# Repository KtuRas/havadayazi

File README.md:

<h1>Arduino ile Havada Yazı</h1>

<p>Bu proje Arduino Günü için oluşturulmuştur.</p>
<p>Kendi etrafında dönebilen bir mekanızmaya bağlı 8 ledin, dönüş sırasında belirli bir düzene göre yüksek
    hızda yanıp sönmesi ile havada yazı oluşturma prensibine göre çalışır.
</p>
<p>Mekanizma dururken ledler yanıp sönsede yazıyı göz ile ayırt edebilmek mümkün değildir. Ancak mekanızma döndürülünce 
    ledler havada farklı yerlerde yanıp söneceğinden göz ile algılayabilmek mümkün olmaktadır.    
</p>

## Çalışma Prensibi
<p>Bir harf aşağıdaki şekilde Arduino' nun çıkışına aktarılmıştır. </p>

<table style="width: 197px; height: 207px;">
<tbody>
<tr>
<td style="width: 32px;">A&nbsp;</td>
<td style="width: 32px;">B&nbsp;</td>
<td style="width: 33px;">&nbsp;C</td>
<td style="width: 33px;">&nbsp;D</td>
<td style="width: 33px;">&nbsp;E</td>
<td style="width: 33px;">&nbsp;F</td>
</tr>
<tr>
<td style="width: 32px;">&nbsp;0</td>
<td style="width: 32px;">&nbsp;1</td>
<td style="width: 33px;">&nbsp;1&nbsp;</td>
<td style="width: 33px;">&nbsp;1&nbsp;</td>
<td style="width: 33px;">&nbsp;1&nbsp;</td>
<td style="width: 33px;">&nbsp;0&nbsp;</td>
</tr>
<tr>
<td style="width: 32px;">&nbsp;1&nbsp;</td>
<td style="width: 32px;">&nbsp;0</td>
<td style="width: 33px;">&nbsp;0&nbsp;</td>
<td style="width: 33px;">&nbsp;0</td>
<td style="width: 33px;">&nbsp;0&nbsp;</td>
<td style="width: 33px;">&nbsp;1&nbsp;</td>
</tr>
<tr>
<td style="width: 32px;">&nbsp;1&nbsp;</td>
<td style="width: 32px;">&nbsp;0&nbsp;</td>
<td style="width: 33px;">&nbsp;0&nbsp;</td>
<td style="width: 33px;">&nbsp;0&nbsp;</td>
<td style="width: 33px;">&nbsp;0&nbsp;</td>
<td style="width: 33px;">&nbsp;1&nbsp;</td>
</tr>
<tr>
<td style="width: 32px;">&nbsp;1&nbsp;</td>
<td style="width: 32px;">&nbsp;1&nbsp;</td>
<td style="width: 33px;">&nbsp;1&nbsp;</td>
<td style="width: 33px;">&nbsp;1&nbsp;</td>
<td style="width: 33px;">&nbsp;1&nbsp;</td>
<td style="width: 33px;">&nbsp;1&nbsp;</td>
</tr>
<tr>
<td style="width: 32px;">&nbsp;1&nbsp;</td>
<td style="width: 32px;">&nbsp;0&nbsp;</td>
<td style="width: 33px;">&nbsp;0&nbsp;</td>
<td style="width: 33px;">&nbsp;0&nbsp;</td>
<td style="width: 33px;">&nbsp;0&nbsp;</td>
<td style="width: 33px;">&nbsp;1&nbsp;</td>
</tr>
<tr>
<td style="width: 32px;">&nbsp;1&nbsp;</td>
<td style="width: 32px;">&nbsp;0&nbsp;</td>
<td style="width: 33px;">&nbsp;0&nbsp;</td>
<td style="width: 33px;">&nbsp;0&nbsp;</td>
<td style="width: 33px;">&nbsp;0&nbsp;</td>
<td style="width: 33px;">&nbsp;1&nbsp;</td>
</tr>
<tr>
<td style="width: 32px;">&nbsp;1&nbsp;</td>
<td style="width: 32px;">&nbsp;0&nbsp;</td>
<td style="width: 33px;">&nbsp;0&nbsp;</td>
<td style="width: 33px;">&nbsp;0&nbsp;</td>
<td style="width: 33px;">&nbsp;0&nbsp;</td>
<td style="width: 33px;">&nbsp;1&nbsp;</td>
</tr>
<tr>
<td style="width: 32px;">&nbsp;0&nbsp;</td>
<td style="width: 32px;">&nbsp;0&nbsp;</td>
<td style="width: 33px;">&nbsp;0</td>
<td style="width: 33px;">&nbsp;0&nbsp;</td>
<td style="width: 33px;">&nbsp; 0</td>
<td style="width: 33px;">&nbsp;0&nbsp;</td>
</tr>
</tbody>
</table>
<!-- DivTable.com -->

<p>
    A, B, C, D, E, F ile kodlandmış her sutün için pinlere yazılacak byte değeri şu şekilde
    hesaplanır.
</p>
<span>

        A: 0xE7

        B: 0x90

        C: 0x90

        D: 0x90

        E: 0xE7
</span>

<p>
    Döner mekanizmanın altında belirlenen bir noktaya yerleştirilen mıknatıslar ve bu mıknatısları 
    algılayacak bir reed röle ile yazının hep aynı noktadan başlamasını ve daha okunaklı görünmesini
    sağladık. Ayrıca bu mıktanıs dönen mekanızmanın hızının değişmesi ile yazının genişliğini
    değiştirme olanağı da sağlamaktadır.
</p>

<p>
    Yazılım içerisindeki Seri haberleşme eklentisi ile yazının ve yazının renginin uzaktan 
    değiştirilmesi sağlanmıştır.
</p>

<p>Devre çizimleri /design klasörünün altta mevcuttur.</p>

<p>Örnek çalışma videosuna <a href="https://www.instagram.com/p/BirVfcIHgj9/?taken-by=ieeektu" target="_blank">bağlantıdan 
ulaşabilirsiniz.</a> </p>

<p>...</p>

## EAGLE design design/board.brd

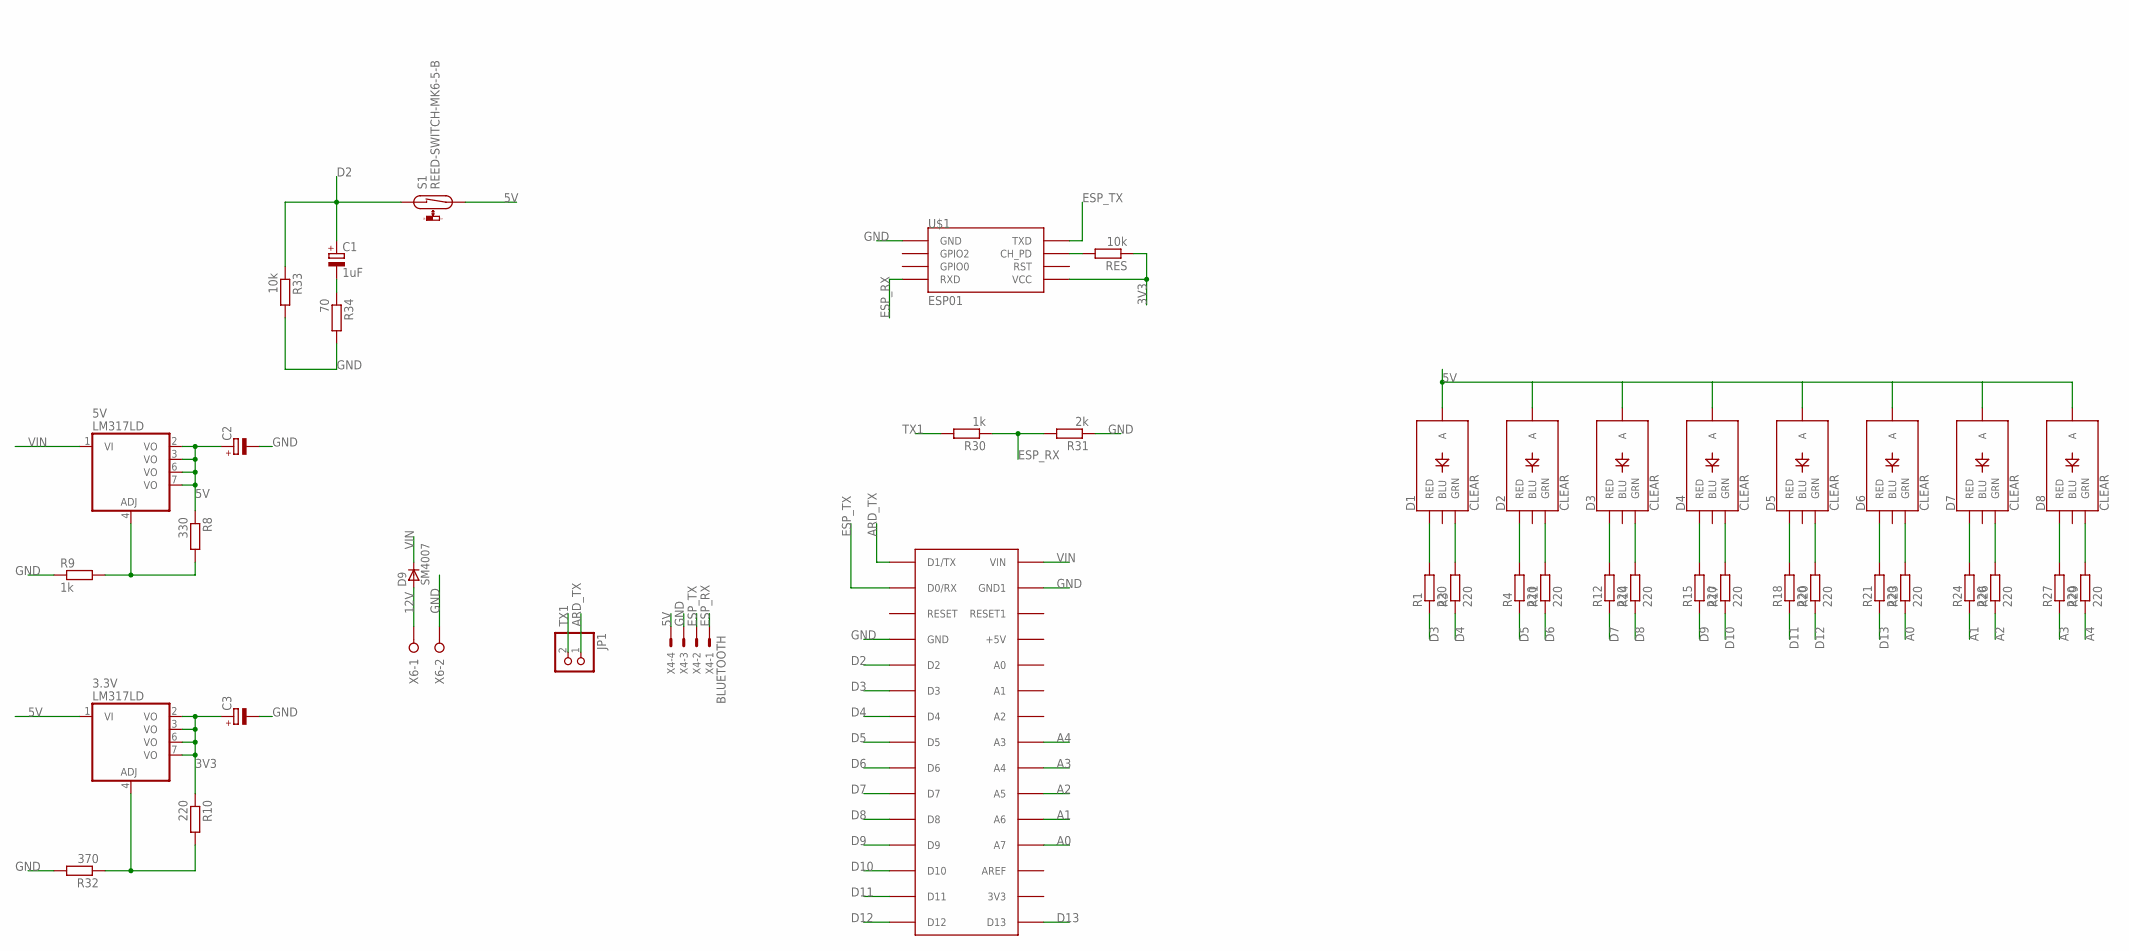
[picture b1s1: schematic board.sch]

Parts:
3.3V, 5V: LM317LD; SO08
C1: 1uF; E2-4
C2, C3: CPOL-EUE2-5; E2-5
D1, D2, D3, D4, D5, D6, D7, D8: CLEAR; LED-RGB-THRU
D9: SM4007; MELF-MLL41_DO213AB
JP1: PINHD-1X2; 1X02
R1, R3, R4, R10, R11, R12, R14, R15, R17, R18, R20, R21, R23, R24, R26, R27, R29: 220; R1206
R8: 330; R1206
R9, R30: 1k; R1206
R31: 2k; R1206
R32: 370; R1206
R33: 10k; R1206
R34: 70; R1206
RES: 10k; R1206
S1: REED-SWITCH-MK6-5-B; MK6-5
U$1: ESP01
U$2: ARDUINONANO; PDIP-32
X4: BLUETOOTH; 22-23-2041
X6: W237-02P; W237-132

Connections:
3V3: 3.3V.2 (VO), 3.3V.3 (VO), 3.3V.6 (VO), 3.3V.7 (VO), C3.+, R10.1, RES.1, U$1.VCC
5V: 3.3V.1 (VI), 5V.2 (VO), 5V.3 (VO), 5V.6 (VO), 5V.7 (VO), C2.+, D1.2 (A), D2.2 (A), D3.2 (A), D4.2 (A), D5.2 (A), D6.2 (A), D7.2 (A), D8.2 (A), R8.1, S1.2, X4.4
12V: D9.A, X6.1
A0: R23.1, U$2.A7
A1: R24.1, U$2.A6
A2: R26.1, U$2.A5
A3: R27.1, U$2.A4
A4: R29.1, U$2.A3
ARD_TX: JP1.1, U$2.D1/TX
D2: C1.+, R33.1, S1.1, U$2.D2
D3: R1.1, U$2.D3
D4: R3.1, U$2.D4
D5: R4.1, U$2.D5
D6: R11.1, U$2.D6
D7: R12.1, U$2.D7
D8: R14.1, U$2.D8
D9: R15.1, U$2.D9
D10: R17.1, U$2.D10
D11: R18.1, U$2.D11
D12: R20.1, U$2.D12
D13: R21.1, U$2.D13
ESP_RX: R30.1, R31.2, U$1.RX (RXD), X4.1
ESP_TX: U$1.TX (TXD), U$2.D0/RX, X4.2
GND: C2.-, C3.-, R9.1, R31.1, R32.2, R33.2, R34.2, U$1.GND, U$2.GND, U$2.GND1, X4.3, X6.2
unnamed: C1.-, R34.1
unnamed: D1.1 (RED), R1.2
unnamed: RES.2, U$1.CH_PD
unnamed: D1.3 (GRN), R3.2
unnamed: D2.1 (RED), R4.2
unnamed: D2.3 (GRN), R11.2
unnamed: D3.1 (RED), R12.2
unnamed: D3.3 (GRN), R14.2
unnamed: D4.1 (RED), R15.2
unnamed: D4.3 (GRN), R17.2
unnamed: D5.1 (RED), R18.2
unnamed: D5.3 (GRN), R20.2
unnamed: D6.1 (RED), R21.2
unnamed: D6.3 (GRN), R23.2
unnamed: D7.1 (RED), R24.2
unnamed: D7.3 (GRN), R26.2
unnamed: D8.1 (RED), R27.2
unnamed: D8.3 (GRN), R29.2
unnamed: 5V.4 (ADJ), R8.2, R9.2
unnamed: 3.3V.4 (ADJ), R10.2, R32.1
TX1: JP1.2, R30.2
VIN: 5V.1 (VI), D9.C, U$2.VIN

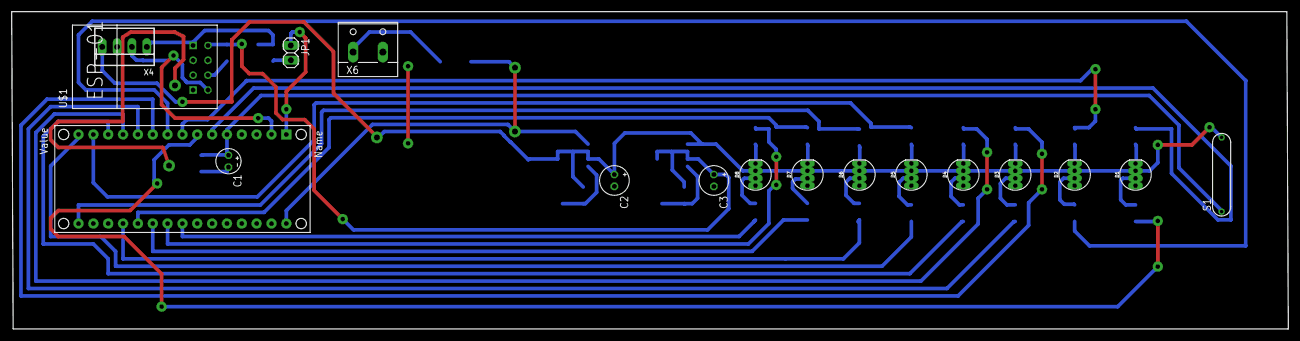
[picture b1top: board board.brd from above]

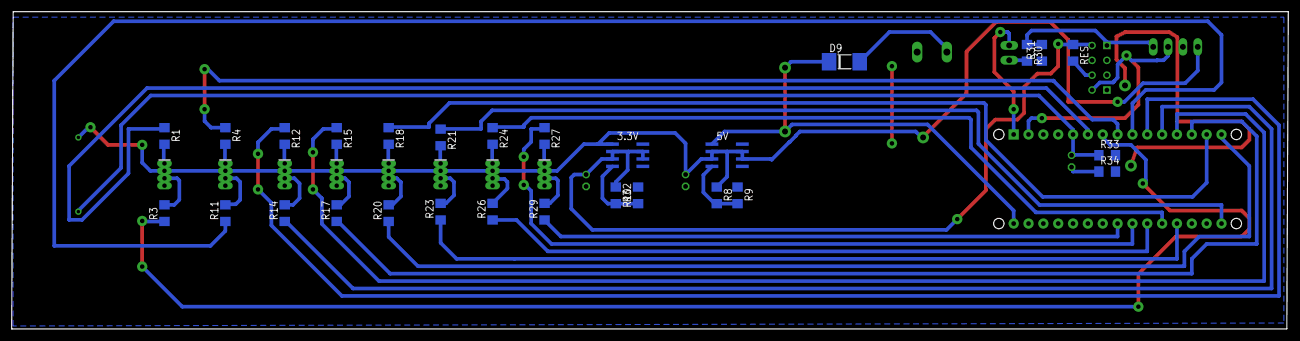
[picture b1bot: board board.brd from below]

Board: 2 copper layers, 218.4 x 54.3 mm, 45 parts (28 on the bottom side), 46 nets.

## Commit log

2018-06-09 readmeV1.0
2018-06-30 readmeV1.1
2018-06-30 add gif
2018-06-30 readme v1.2

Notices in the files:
parts and their libraries:
SparkFun-LED: Licensing: Creative Commons ShareAlike 4.0 International - https://creativecommons.org/licenses/by-sa/4.0
